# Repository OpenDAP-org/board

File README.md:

# Board

OpenDAP main board (SBC): the SoC-based single board computer, its auxiliary MCUs and simulations.

## Layout

- `hardware/`
- `firmware/`
- `sim/`
- `export/`
- `docs/`

## License

This repository follows the [REUSE](https://reuse.software) layout: license texts live in `LICENSES/` and `REUSE.toml` maps each path to its license.

- Default: **Creative Commons Attribution-ShareAlike 4.0** (`CC-BY-SA-4.0`)
- `hardware/`: **CERN Open Hardware Licence v2 – Strongly Reciprocal** (`CERN-OHL-S-2.0`)
- `firmware/`: **MIT** (`MIT`)
- `sim/`: **GNU GPL v3.0 or later** (`GPL-3.0-or-later`)
- `export/`: **CERN Open Hardware Licence v2 – Weakly Reciprocal** (`CERN-OHL-W-2.0`)
- `docs/`: **Creative Commons Attribution-ShareAlike 4.0** (`CC-BY-SA-4.0`)

Copyright © 2026 The OpenDAP Project.

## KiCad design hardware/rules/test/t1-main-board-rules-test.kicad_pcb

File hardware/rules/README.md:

# Main board rules

The T1 main board's own design rules, from the [PCB design constraints](../../docs/specs/pcb-design-constraints.md) (BRD-060) and the [DFM and reliability rules research](../../docs/research/2026-10-pcb-dfm-reliability-rules.md).

- `t1-main-board.kicad_dru`: the product rules. Each rule is named after the constraint it enforces and the lowest quality level at which it is mandatory ([RFC 0010](https://github.com/opendap-project/rfcs/blob/main/text/0010-quality-levels.md)): `T1 PCB-H-01 [Q1]: …`.
- `netclasses.toml`: the net classes the rules and the schematic share, with their constraint IDs, design currents and impedance targets.
- `test/`: a test board with one failing and one passing object per rule, built by `make_test_board.py` on kicad-lib's test-board tools (submodule `../lib/opendap`).

The KiCad project's rules, [`../t1-main-board/t1-main-board.kicad_dru`](../t1-main-board/), are the composition of the PCBWay HDI fab rules (kicad-lib `design-rules/pcbway-hdi`), the OpenDAP craft rules (kicad-lib `design-rules/opendap-craft`) and these product rules, in that order, made and checked with `odapkit dru` (E3.5) from `t1-main-board.dru.toml`.

Impedance-controlled net classes are named `<name>_<ohms>D` (differential) or `<name>_<ohms>SE` (single-ended), so the craft rules exempt them from their general width rules (CRAFT-40, CRAFT-43; the composition was checked with every impedance class: no craft or fab report on their tracks). The product rules find the same classes with the same wildcards (PCB-S-14, PCB-W-01).

## Layers

The board is the 10-layer [stackup v1](../../docs/specs/stackup-v1.md). The rules name KiCad's layers:

| Stackup | L1 | L2 | L3 | L4 | L5 | L6 | L7 | L8 | L9 | L10 |
|---|---|---|---|---|---|---|---|---|---|---|
| KiCad | `F.Cu` | `In1.Cu` | `In2.Cu` | `In3.Cu` | `In4.Cu` | `In5.Cu` | `In6.Cu` | `In7.Cu` | `In8.Cu` | `B.Cu` |
| Role | signal | ground | signal | ground | power | power | ground | signal | ground | signal |

Per-class widths are rules on `(layer outer)` (L1, L10) and `(layer inner)` (L3, L8); PCB-S-14 keeps impedance classes off every other inner layer, so "inner" means L3 and L8 for them. Each width rule is min / opt / max = the stackup width −5 % / exact / +5 %: a 5 % width error moves the impedance by 2–3 % (stackup v1 §5.1), a third of PCBWay's ±10 % window, so the rule catches a wrong width while the fab's own corners keep the rest. The minimum never goes below 0.075 mm, PCBWay's published HDI 3/3 mil option; for those classes the rules replace the fab set's 3 mil (0.0762 mm) track rule, which the inner 100 Ω width (75.0 µm) would otherwise break. Pair gaps are a clearance between the two nets of a pair at the gap −5 %, never below 0.1 mm. Every width and gap is **UNVERIFIED** (a warning) until PCBWay's DFM review confirms the stackup.

## Severity

- A rule at Q0 or Q1 whose value has a source is an **error**.
- A rule at Q2 to Q4 is a **warning**, whatever its source (RFC 0010: items above the build's target level are debt, not blockers).
- A rule whose value is still **UNVERIFIED** is a **warning** at any level, and becomes an error when the value is sourced and the level is Q0 or Q1.

Each rule's comment in the `.kicad_dru` names its source; the research note lists primary and secondary sources per rule.

## Conventions the rules rely on

The rules find objects by reference prefix, footprint field, pad fabrication property and rule-area name. The schematic symbols and footprints carry them; a footprint that does not follow them escapes its rules.

| Object | Convention | Rules |
|---|---|---|
| Mounting hole | Footprint reference `H*` (`H1`…`H4`); one pad, NPTH or plated | PCB-H-01 to H-06 |
| Ceramic capacitor (MLCC) | Reference `C*`. A capacitor that is not an MLCC still gets the MLCC rules, which only cost distance | PCB-H-05, PCB-B-03 |
| Edge-mounted part | Reference `J*` (connectors) or `SW*` (side buttons): exempt from the part-to-edge rule, may overhang the edge | PCB-B-01 |
| BGA needing rework access | Footprint field `Rework` = `BGA` (RK3566, LPDDR4X, eMMC) | PCB-D-01 |
| BGA ball pads | Pad fabrication property "BGA pad" (also used by the fab rules) | PCB-H-06 |
| Fiducial | Reference `FID*`; pad fabrication property "Fiducial, global to board" or "Fiducial, local to footprint" | PCB-D-02 to D-04 |
| Test point | Reference `TP*`; pad fabrication property "Test point pad" | PCB-D-06 to D-09 |
| Via in a pad | Via property Filling = Filled and Capping = Capped (IPC-4761 type VII) | PCB-D-10 |
| Heat source | Footprint field `Thermal` = `hot` (converters, eFuses, charger, SoC, PMIC) | PCB-L-01 |
| Battery pocket | Rule area `BATTERY_POCKET`: the pocket's footprint on the board, grown by a 3 mm margin (**UNVERIFIED**) | PCB-L-01 |
| Battery contacts | Rule area `BATTERY_CONNECTOR`: the pocket-floor contact window plus 1 mm, around the six battery contacts and their unfused copper (ADR 0020) | PCB-L-02, L-05 |
| Battery nets | Net classes `PWR_BAT` (P+, P−) and `BAT_SENSE` (mid-cell tap, NTC) in `netclasses.toml` | PCB-L-02, L-05 |
| Empty contact position | Rule area `BATTERY_CONTACT_EMPTY`: the 7.00 × 2.70 mm pad position left empty between P+ and the mid-cell tap | PCB-L-04 |
| Battery contact ESD | Footprint field `ESD` = `battery` on the TPD1E10B06 of the mid-cell tap and NTC; rule area `BATTERY_ESD`: the contact pads grown by 3 mm (**UNVERIFIED**) | PCB-L-08 |
| Panel break tab | Rule area `BREAK_TAB` around each tab or mouse-bite position on the outline, reaching at least 5.08 mm (PCB-B-03) into the board | PCB-B-02, B-03 |
| RK3566 escape | Rule area `BGA_ESCAPE` (existing) | PCB-G-02, W-01, V-01 |
| Analog audio | Rule area `AUDIO_ANALOG` (existing) | PCB-A-07 |
| Differential pair | Net names ending in `_P` / `_N` (or `+` / `-`), so KiCad couples the pair | PCB-I-01 to I-05, I-12 (pair gap) |
| RF ground cut-out | Rule area `RF_CUTOUT`: the L2 (L9) cut-out under the RF line, 1.6 mm wide and 0.6 mm past each end, on the cut layer and the pour layer of the line's side only (`In1.Cu` + `In2.Cu` for an L1 line, `In8.Cu` + `In7.Cu` for L10), with "keep out copper fills" set so the plane's fill stays out | PCB-R-03 |

## Check

```sh
PY=/Applications/KiCad/KiCad.app/Contents/Frameworks/Python.framework/Versions/Current/bin/python3
$PY hardware/rules/test/make_test_board.py
python3 hardware/lib/opendap/design-rules/tools/check_drc.py hardware/rules/test/t1-main-board-rules-test.kicad_pcb
```

Every rule fires exactly once in the FAIL column and nothing fires in the PASS column.

Rules that overlap the fab and craft rule sets are left to them: silkscreen to pads and vias, silk sizes, 45° routing, acute angles (CRAFT-41, 135° minimum), short segments and the via set live in kicad-lib `opendap-craft`. The composition `pcbway-hdi` + `opendap-craft` + these rules compiles under KiCad 10.0.7 with every T1 rule still firing on the test board. The test board has ten copper layers; its GND objects are joined by a bus on L7 (`In6.Cu`), which no rule constrains, so the board reports no unconnected items.

## Not checked by DRC

Impedance itself, the maximum pair gap, spacing to other nets (3–5 × W), length matching, skew and delay matching across layers (PCB-I, PCB-S-15), height zones (PCB-Z, including the battery-contact exception of PCB-L-05), copper area per net and via counts for current (PCB-P-01 to PCB-P-03, PCB-P-09), the battery contacts' pad size, pitch and order (PCB-L-04), via count per contact pad and pour symmetry (PCB-L-07), ESD distance (PCB-E-01) and test-pad coverage (PCB-T-02) are layout checks (E4.5). The contact working height and the liner distance (PCB-L-06) are 3D review and case items. Review items are listed in the specification.

KiCad 10.0.7 can express three more rules, thermal-relief spoke count (`min_resolved_spokes`), differential-pair uncoupled length (`diff_pair_uncoupled`) and differential-pair gap (`diff_pair_gap`, with its maximum and the router's gap), but its report does not name the rule for them ("zone min spoke count", "(<rule> maximum uncoupled length", "(<rule> maximum gap"), so `check_drc.py` cannot attribute them. The pair gap's minimum is checked as a clearance instead (see Layers). They wait for a kicad-lib `check_drc.py` that reads those messages; until then they are CHK items in the research note, with the other checks DRC cannot make.

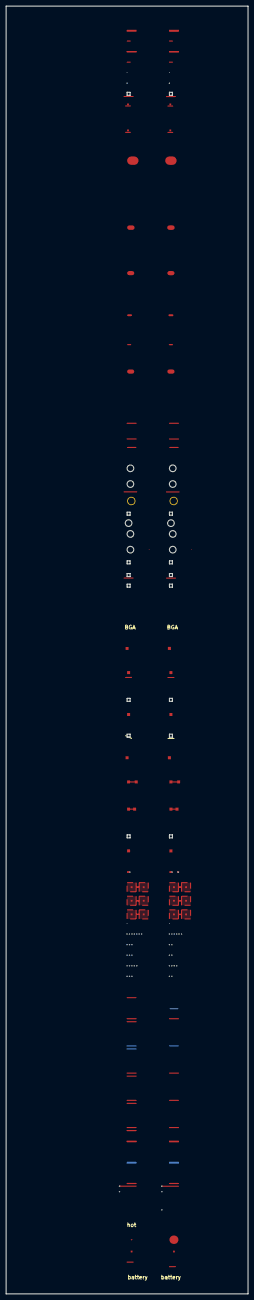
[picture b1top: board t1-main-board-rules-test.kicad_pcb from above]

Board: 10 copper layers, 80.0 x 425.9 mm, 69 parts (0 on the bottom side), 10 nets.

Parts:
C1, C2, C3, C4, C5, C6: test
D1, D2: test
FID1, FID2: test
H1, H2, H3, H4, H5, H6, H7, H8, H9, H10, H11, H12: test
R1, R2, R3, R4, R5, R6, R7, R8, R9, R10, R11, R12, R13, R14, R15, R16, R17, R18, R19, R20, R21, R22, R23, R24, R25, R26, R27: test
TP1, TP2, TP3, TP4, TP5, TP6, TP7, TP8, TP9, TP10, TP11, TP12, TP13, TP14: test
U1, U2, U3, U4, U5, U6: test

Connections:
DDR_50SE_1: R18.1, R19.1
DDR_50SE_2: R20.1, R21.1
N45: TP7.1, TP8.1
N46: TP9.1, TP10.1
N47: R9.1, TP11.1
N48: R10.1, TP12.1
N54: R14.1, R15.1
N55: R16.1, R17.1
N56: R22.1, R23.1
N57: R24.1, R25.1
